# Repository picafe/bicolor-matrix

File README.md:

# bicolor-matrix

> **This repository has moved to [bicolor-matrix-v2](https://github.com/picafe/bicolor-matrix-v2).**

A 32x8 bicolor LED matrix module composed of 4 8x8 matrices based on the Holtek HT16K33A I2C LED driver.

## Inspiration

Inspired by the common 32x8 red LED matrix modules that use the MAX7219 IC, I wanted to make my own module but with more colours and functionality, while keeping the same asthetic. 

I found [these](https://www.aliexpress.com/item/1005007029570407.html) modules while browsing Aliexpress and thought they could look be a cool alternative. With the red and light green variant, you can have red, a light green, and orange all in one module. As far as I'm aware, there aren't RGB modules in a similar form factor, although you can take generic WS2818 8x8 matricies and 3D print a diffuser for them, although the footprint is much bigger. This project was also partially inspired by [bitluni's LED magnet tiles](https://www.youtube.com/watch?v=L2J_eNgjxio) which I found really cool.

Unlike the single colour matricies with 16 pins, these had 24. I found [this](https://www.adafruit.com/product/902) Adafruit module and followed a similar schematic with the Holtek HT16K33A I2C LED driver, but with an inverted board layout, and with 4 modules on one PCB. This was my 2nd PCB project, so it was definately a big undertaking.

## Showcase

Matrix Board:

Adapter Board:
This adds functionality through a RP2040 Zero board, a DS3231 module and a small buzzer, and a generic logic level shifter since the Holtek IC only operates near 5V.

Button Board:
An addition to the adapter board and provides 4 interface buttons for setting time

## Bill of Materials (BOM) + Assembly Notes
Item | Quantity | Description
| -------- | ------- | ------- |
[Machine Pin Headers](https://www.aliexpress.com/item/10000000838267.html) | 5 Pcs | 2.54mm pitch circular pin headers to connect the LED matricies to the main PCB. These are needed such as to not solder the matrix boards directly to the PCB, allowing for easier replacement if needed.
12mm x 12mm Buttons | 4 | Generic 12mm tactile push buttons, whatever is cheapest on Aliexpress. I used [these](https://www.aliexpress.com/item/10000000838267.html).
RP2040 Zero | 1 | Microcontroller board, whatever is cheapest on Aliexpress. I bought from [here](https://www.aliexpress.com/item/1005007650325892.html).
[DS3231 Module](https://www.aliexpress.com/item/1005007143842437.html) | 1 | Mini module without the battery, basically a simple breakout. Use side cutters to cut the plastic on the pre-soldered female headers, then desolder each of the pins. Solder in male headers.
Level Shifter | 1 | 4-channel logic level shifter module, whatever is cheapest on Aliexpress. They are cheapest in packs of 10, so you can use the extra ones for other projects. I bought from [here](https://www.aliexpress.com/item/1005006765742290.html).
Buzzer | 1 | Generic 3.3V 7.6mm diameter buzzer, whatever is cheapest on Aliexpress.
[Right Angle Pin Headers](https://www.aliexpress.com/item/32896209964.html) | 1 | Get the R1 type of pin headers pictured here, they're slightly more uncommon and more expensive than the R1 type. This is for the button board connection. 
2.54mm Pin Headers (Male and Female) | 1 | To connect the matrix board to the adapter board and general use. This [video](https://www.youtube.com/watch?v=qDG3VFSMSPQ) shows how to make custom length female headers.

Buying Note: I recommend you try to buy components on the Aliexpress mobile app (web on desktop doesn't seem to have a search bar) in Bundle Deals if you can find them as you can get better prices, and they usually ship faster.

Ordering Note: I recommend you to create your own adapter board for the project. The one I built has some design flaws (button board doesn't fit flush with the adapter board, the right angle headers need to be positioned lower, and usb connector placement could be improved).

It was designed to be a prototype and optimize costs, so I recommend you to make your own design based on your needs. I was browsing Aliexpress a few days ago and found this [RP2350 stamp module](https://www.aliexpress.com/item/1005008513193739.html) which would make a better alternative since you can position the USB connector anywhere on the PCB. It's also relatively cheap.

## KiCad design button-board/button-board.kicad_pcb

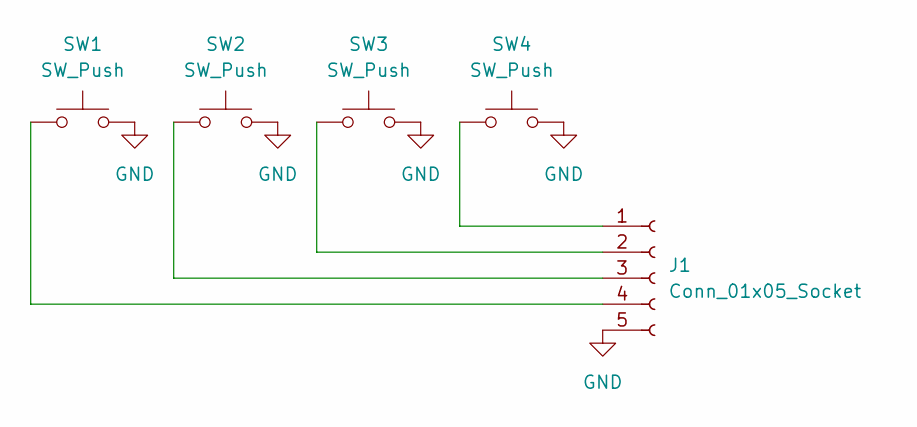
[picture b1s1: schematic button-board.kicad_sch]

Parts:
J1: Conn_01x05_Socket; PinSocket_1x05_P2.54mm_Vertical
SW1, SW2, SW3, SW4: SW_Push; SW_PUSH-12mm

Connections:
GND: J1.5, SW1.2, SW2.2, SW3.2, SW4.2
unnamed: J1.1, SW4.1
unnamed: J1.2, SW3.1
unnamed: J1.3, SW2.1
unnamed: J1.4, SW1.1

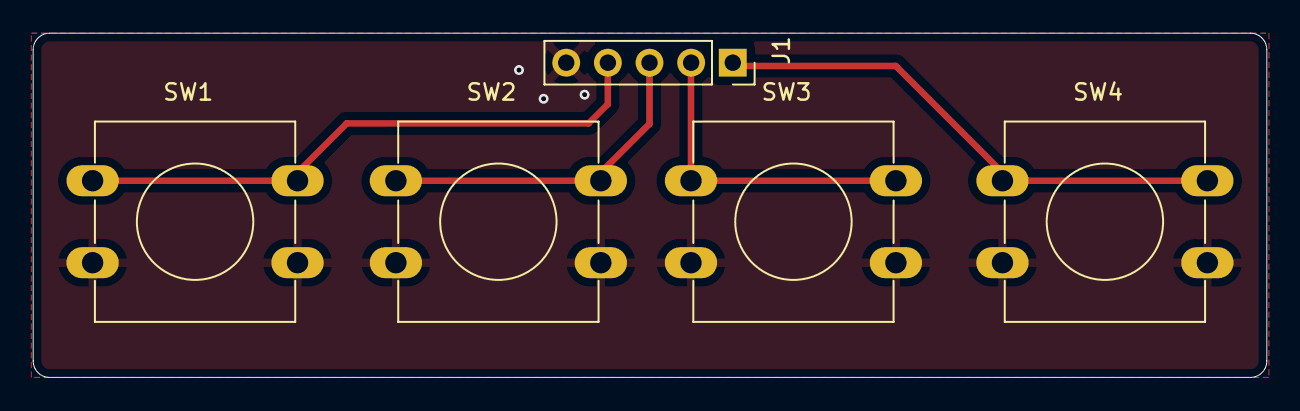
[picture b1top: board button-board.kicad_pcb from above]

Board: 2 copper layers, 75.3 x 21.0 mm, 5 parts (0 on the bottom side), 5 nets.

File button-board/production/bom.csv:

Designator,Footprint,Quantity,Value,LCSC Part #
J1,PinSocket_1x05_P2.54mm_Vertical,1,Conn_01x05_Socket,
"SW1, SW2, SW3, SW4",SW_PUSH-12mm,4,SW_Push,

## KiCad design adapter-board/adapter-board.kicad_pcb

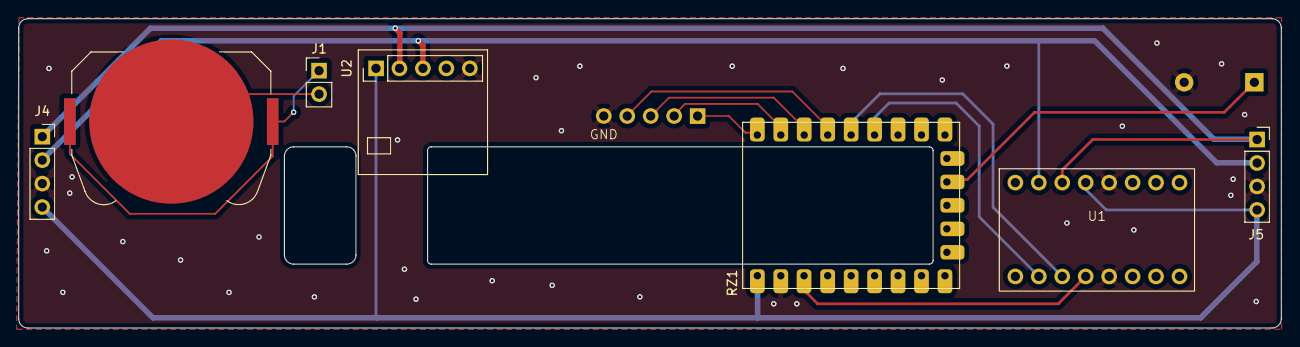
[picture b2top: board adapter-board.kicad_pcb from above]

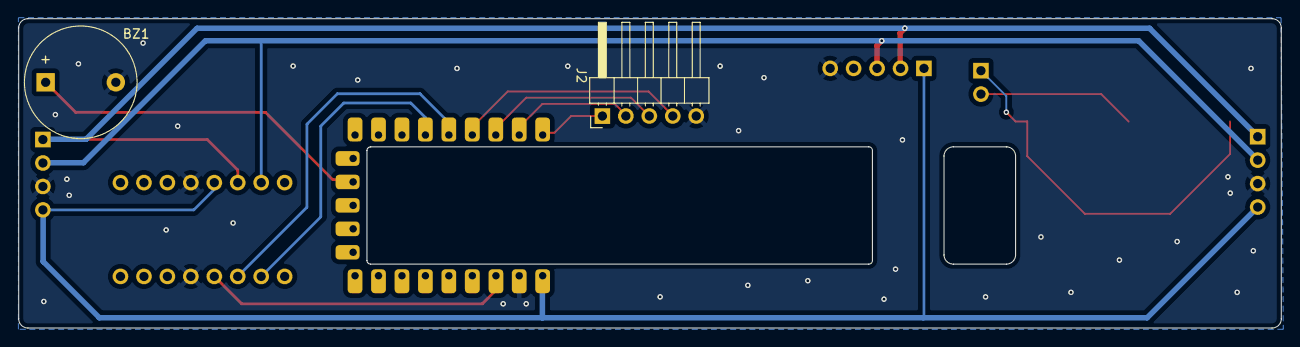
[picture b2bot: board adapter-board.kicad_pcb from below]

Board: 2 copper layers, 136.8 x 33.5 mm, 9 parts (2 on the bottom side), 12 nets.

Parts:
BT1: Battery_Cell; BatteryHolder_Keystone_3034_1x20mm
BZ1: Buzzer; Buzzer_12x9.5RM7.6
J1: Conn_01x02_Socket; PinHeader_1x02_P2.54mm_Vertical
J2: Conn_01x05_Pin; PinHeader_1x05_P2.54mm_Horizontal
J4, J5: Conn_01x04_Socket; PinSocket_1x04_P2.54mm_Vertical
RZ1: RP2040-Zero
U1: Generic-Level-Shifter
U2: PinHeader_1x05_P2.54mm_Vertical

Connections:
3V3: RZ1.21 (3V3), U1.9 (LV)
GND: BZ1.2 (-), J2.5, J4.3, J5.3, RZ1.22 (GND), U1.4 (GND), U1.10 (GND), U2.5 (GND)
unnamed: BZ1.1 (+), RZ1.11 (GP10)
unnamed: J2.1, RZ1.1 (GP0)
unnamed: J2.2, RZ1.2 (GP1)
unnamed: J2.3, RZ1.3 (GP2)
unnamed: J2.4, RZ1.4 (GP3)
unnamed: J4.1, J5.1, U1.2 (HV2), U2.2 (SDA)
unnamed: J4.2, J5.2, U1.1 (HV1), U2.3 (SCL)
unnamed: RZ1.5 (GP4), U1.8 (LV2)
unnamed: RZ1.6 (GP5), U1.7 (LV1)
VUSB: J4.4, J5.4, RZ1.23 (5V), U1.3 (HV), U2.1 (VCC)

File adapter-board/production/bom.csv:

Designator,Footprint,Quantity,Value,LCSC Part #
BT1,BatteryHolder_Keystone_3034_1x20mm,1,Battery_Cell,
BZ1,Buzzer_12x9.5RM7.6,1,Buzzer,
J1,PinHeader_1x02_P2.54mm_Vertical,1,Conn_01x02_Socket,
J2,PinHeader_1x05_P2.54mm_Horizontal,1,Conn_01x05_Pin,
"J4, J5",PinSocket_1x04_P2.54mm_Vertical,2,Conn_01x04_Socket,
RZ1,RP2040-Zero,1,RP2040-Zero,
U1,Generic-Level-Shifter,1,~,
U2,PinHeader_1x05_P2.54mm_Vertical,1,~,

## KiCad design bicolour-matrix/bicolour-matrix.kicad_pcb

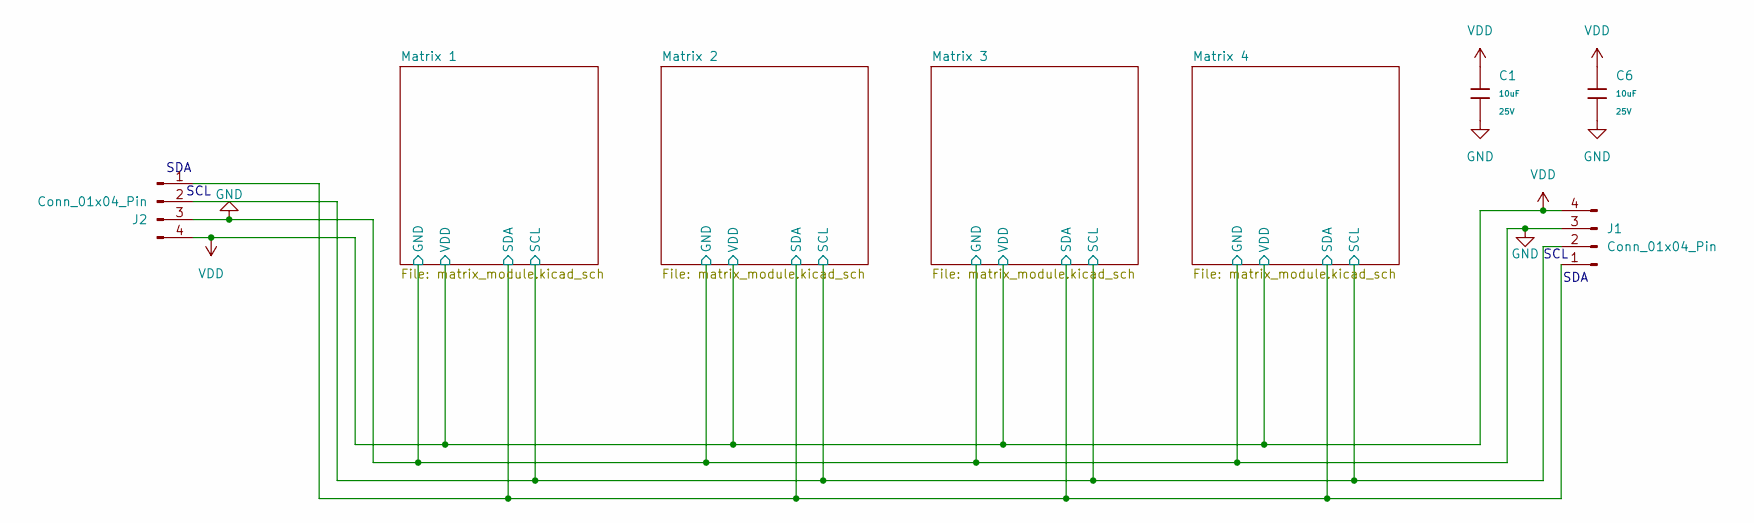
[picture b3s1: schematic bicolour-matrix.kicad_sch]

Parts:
C1, C6: 10uF; C_0805; Voltage Rated 25V; Tolerance ±10%; Part CL21A106KAYNNNE; LCSC C15850
J1, J2: Conn_01x04_Pin; PinHeader_1x04_P2.54mm_Vertical

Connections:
/Matrix 1/SCL: J1.2, J2.2; also elsewhere on the board
/Matrix 1/SDA: J1.1, J2.1; also elsewhere on the board
GND: C1.2, C6.2, J1.3, J2.3; also elsewhere on the board
VDD: C1.1, C6.1, J1.4, J2.4; also elsewhere on the board

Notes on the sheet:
SCL
SDA

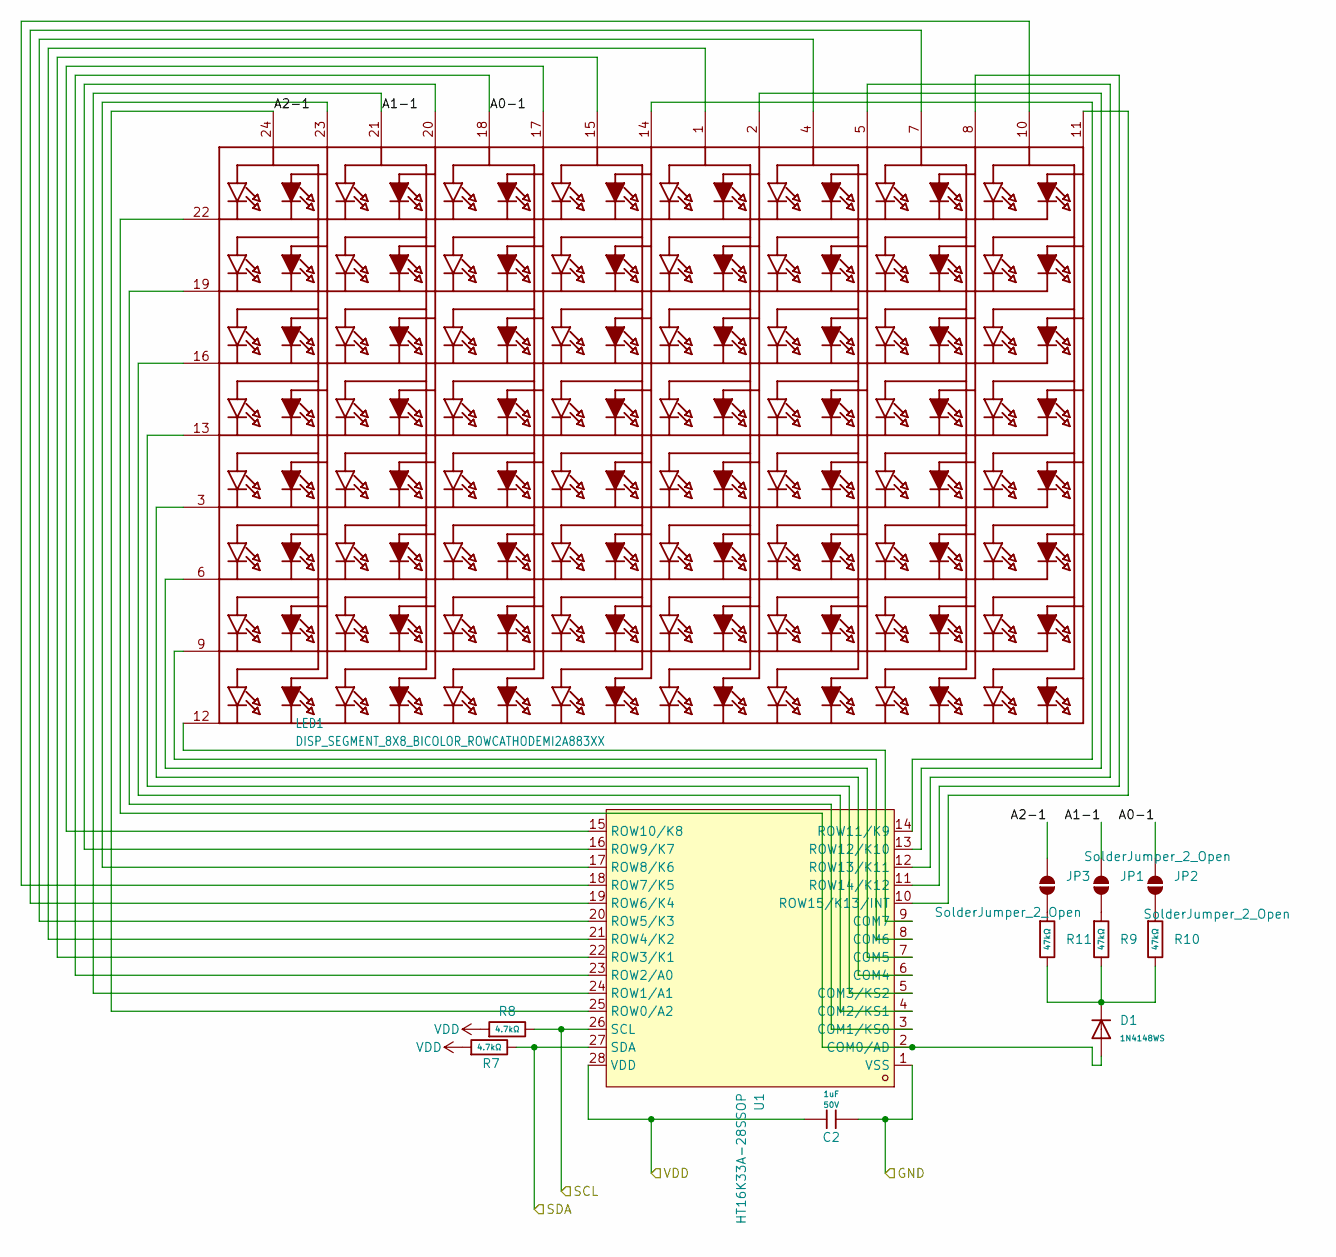
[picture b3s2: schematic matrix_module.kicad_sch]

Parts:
C2: 1uF; C_0603; Voltage Rated 50V; Tolerance ±10%; Part CL10A105KB8NNNC; LCSC C15849
D1: 1N4148WS; D_SOD-323; Forward Voltage (Vf@If) 1.25V@150mA; Reverse Voltage (Vr) 100V; Part 1N4148WS; LCSC C2128
JP1, JP2, JP3: SolderJumper_2_Open; SolderJumper-2_P1.3mm_Open_RoundedPad1.0x1.5mm
LED1: DISP_SEGMENT_8X8_BICOLOR_ROWCATHODEMI2A883XX; SEGMENT_BICOL_BL-M12A883XX
R7, R8: 4.7kΩ; R_0603; Overload Voltage (Max) 75V; Tolerance ±1%; Part 0603WAF4701T5E; LCSC C23162
R9, R10, R11: 47kΩ; R_0603; Overload Voltage (Max) 75V; Tolerance ±1%; Part 0603WAF4702T5E; LCSC C25819
U1: HT16K33A-28SSOP; SSOP-28_3.9x9.9mm_P0.635mm; LCSC Part C5444738

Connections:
/Matrix 1/A0-1: JP2.2 (B), LED1.18 (A5), U1.23 (ROW2/A0)
/Matrix 1/A1-1: JP1.2 (B), LED1.21 (A3), U1.24 (ROW1/A1)
/Matrix 1/A2-1: JP3.2 (B), LED1.24 (A1), U1.25 (ROW0/A2)
/Matrix 1/SCL: R8.2, U1.26 (SCL); also elsewhere on the board
/Matrix 1/SDA: R7.2, U1.27 (SDA); also elsewhere on the board
GND: C2.2, U1.1 (VSS); also elsewhere on the board
unnamed: D1.1, R9.2, R10.2, R11.2
unnamed: JP1.1 (A), R9.1
unnamed: JP2.1 (A), R10.1
unnamed: JP3.1 (A), R11.1
unnamed: LED1.23 (A2), U1.17 (ROW8/K6)
unnamed: LED1.20 (A4), U1.16 (ROW9/K7)
unnamed: LED1.17 (A6), U1.15 (ROW10/K8)
unnamed: LED1.15 (A7), U1.22 (ROW3/K1)
unnamed: LED1.14 (A8), U1.14 (ROW11/K9)
unnamed: LED1.1 (A9), U1.21 (ROW4/K2)
unnamed: LED1.2 (A10), U1.13 (ROW12/K10)
unnamed: LED1.4 (A11), U1.20 (ROW5/K3)
unnamed: LED1.5 (A12), U1.12 (ROW13/K11)
unnamed: LED1.7 (A13), U1.19 (ROW6/K4)
unnamed: LED1.8 (A14), U1.11 (ROW14/K12)
unnamed: LED1.10 (A15), U1.18 (ROW7/K5)
unnamed: LED1.11 (A16), U1.10 (ROW15/K13/INT)
unnamed: D1.2, LED1.22 (K1), U1.2 (COM0/AD)
unnamed: LED1.19 (K2), U1.3 (COM1/KS0)
unnamed: LED1.16 (K3), U1.4 (COM2/KS1)
unnamed: LED1.13 (K4), U1.5 (COM3/KS2)
unnamed: LED1.3 (K5), U1.6 (COM4)
unnamed: LED1.6 (K6), U1.7 (COM5)
unnamed: LED1.9 (K7), U1.8 (COM6)
unnamed: LED1.12 (K8), U1.9 (COM7)
VDD: C2.1, R7.1, R8.1, U1.28 (VDD); also elsewhere on the board

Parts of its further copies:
C3, C4, C5: 1uF; C_0603; Voltage Rated 50V; Tolerance ±10%; Part CL10A105KB8NNNC; LCSC C15849
D2, D3, D4: 1N4148WS; D_SOD-323; Forward Voltage (Vf@If) 1.25V@150mA; Reverse Voltage (Vr) 100V; Part 1N4148WS; LCSC C2128
JP4, JP5, JP6, JP7, JP8, JP9, JP10, JP11, JP12: SolderJumper_2_Open; SolderJumper-2_P1.3mm_Open_RoundedPad1.0x1.5mm
LED2, LED3, LED4: DISP_SEGMENT_8X8_BICOLOR_ROWCATHODEMI2A883XX; SEGMENT_BICOL_BL-M12A883XX
R1, R2, R6, R12, R16, R17: 4.7kΩ; R_0603; Overload Voltage (Max) 75V; Tolerance ±1%; Part 0603WAF4701T5E; LCSC C23162
R3, R4, R5, R13, R14, R15, R18, R19, R20: 47kΩ; R_0603; Overload Voltage (Max) 75V; Tolerance ±1%; Part 0603WAF4702T5E; LCSC C25819
U2, U3, U4: HT16K33A-28SSOP; SSOP-28_3.9x9.9mm_P0.635mm; LCSC Part C5444738

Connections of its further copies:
/Matrix 1/SCL: R2.2, R12.2, R17.2, U2.26 (SCL), U3.26 (SCL), U4.26 (SCL); also elsewhere on the board
/Matrix 1/SDA: R1.2, R6.2, R16.2, U2.27 (SDA), U3.27 (SDA), U4.27 (SDA); also elsewhere on the board
/Matrix 2/A0-1: JP6.2 (B), LED2.18 (A5), U2.23 (ROW2/A0)
/Matrix 2/A1-1: JP5.2 (B), LED2.21 (A3), U2.24 (ROW1/A1)
/Matrix 2/A2-1: JP4.2 (B), LED2.24 (A1), U2.25 (ROW0/A2)
/Matrix 3/A0-1: JP9.2 (B), LED3.18 (A5), U3.23 (ROW2/A0)
/Matrix 3/A1-1: JP8.2 (B), LED3.21 (A3), U3.24 (ROW1/A1)
/Matrix 3/A2-1: JP7.2 (B), LED3.24 (A1), U3.25 (ROW0/A2)
/Matrix 4/A0-1: JP12.2 (B), LED4.18 (A5), U4.23 (ROW2/A0)
/Matrix 4/A1-1: JP11.2 (B), LED4.21 (A3), U4.24 (ROW1/A1)
/Matrix 4/A2-1: JP10.2 (B), LED4.24 (A1), U4.25 (ROW0/A2)
GND: C3.2, C4.2, C5.2, U2.1 (VSS), U3.1 (VSS), U4.1 (VSS); also elsewhere on the board
unnamed: D2.1, R3.2, R4.2, R5.2
unnamed: D3.1, R13.2, R14.2, R15.2
unnamed: D4.1, R18.2, R19.2, R20.2
unnamed: JP4.1 (A), R3.1
unnamed: JP5.1 (A), R4.1
unnamed: JP6.1 (A), R5.1
unnamed: JP7.1 (A), R13.1
unnamed: JP8.1 (A), R14.1
unnamed: JP9.1 (A), R15.1
unnamed: JP10.1 (A), R18.1
unnamed: JP11.1 (A), R19.1
unnamed: JP12.1 (A), R20.1
unnamed: LED2.23 (A2), U2.17 (ROW8/K6)
unnamed: LED2.20 (A4), U2.16 (ROW9/K7)
unnamed: LED2.17 (A6), U2.15 (ROW10/K8)
unnamed: LED2.15 (A7), U2.22 (ROW3/K1)
unnamed: LED2.14 (A8), U2.14 (ROW11/K9)
unnamed: LED2.1 (A9), U2.21 (ROW4/K2)
unnamed: LED2.2 (A10), U2.13 (ROW12/K10)
unnamed: LED2.4 (A11), U2.20 (ROW5/K3)
unnamed: LED2.5 (A12), U2.12 (ROW13/K11)
unnamed: LED2.7 (A13), U2.19 (ROW6/K4)
unnamed: LED2.8 (A14), U2.11 (ROW14/K12)
unnamed: LED2.10 (A15), U2.18 (ROW7/K5)
unnamed: LED2.11 (A16), U2.10 (ROW15/K13/INT)
unnamed: D2.2, LED2.22 (K1), U2.2 (COM0/AD)
unnamed: LED2.19 (K2), U2.3 (COM1/KS0)
unnamed: LED2.16 (K3), U2.4 (COM2/KS1)
unnamed: LED2.13 (K4), U2.5 (COM3/KS2)
unnamed: LED2.3 (K5), U2.6 (COM4)
unnamed: LED2.6 (K6), U2.7 (COM5)
unnamed: LED2.9 (K7), U2.8 (COM6)
unnamed: LED2.12 (K8), U2.9 (COM7)
unnamed: LED3.23 (A2), U3.17 (ROW8/K6)
unnamed: LED3.20 (A4), U3.16 (ROW9/K7)
unnamed: LED3.17 (A6), U3.15 (ROW10/K8)
unnamed: LED3.15 (A7), U3.22 (ROW3/K1)
unnamed: LED3.14 (A8), U3.14 (ROW11/K9)
unnamed: LED3.1 (A9), U3.21 (ROW4/K2)
unnamed: LED3.2 (A10), U3.13 (ROW12/K10)
unnamed: LED3.4 (A11), U3.20 (ROW5/K3)
unnamed: LED3.5 (A12), U3.12 (ROW13/K11)
unnamed: LED3.7 (A13), U3.19 (ROW6/K4)
unnamed: LED3.8 (A14), U3.11 (ROW14/K12)
unnamed: LED3.10 (A15), U3.18 (ROW7/K5)
unnamed: LED3.11 (A16), U3.10 (ROW15/K13/INT)
unnamed: D3.2, LED3.22 (K1), U3.2 (COM0/AD)
unnamed: LED3.19 (K2), U3.3 (COM1/KS0)
unnamed: LED3.16 (K3), U3.4 (COM2/KS1)
unnamed: LED3.13 (K4), U3.5 (COM3/KS2)
unnamed: LED3.3 (K5), U3.6 (COM4)
unnamed: LED3.6 (K6), U3.7 (COM5)
unnamed: LED3.9 (K7), U3.8 (COM6)
unnamed: LED3.12 (K8), U3.9 (COM7)
unnamed: LED4.23 (A2), U4.17 (ROW8/K6)
unnamed: LED4.20 (A4), U4.16 (ROW9/K7)
unnamed: LED4.17 (A6), U4.15 (ROW10/K8)
unnamed: LED4.15 (A7), U4.22 (ROW3/K1)
unnamed: LED4.14 (A8), U4.14 (ROW11/K9)
unnamed: LED4.1 (A9), U4.21 (ROW4/K2)
unnamed: LED4.2 (A10), U4.13 (ROW12/K10)
unnamed: LED4.4 (A11), U4.20 (ROW5/K3)
unnamed: LED4.5 (A12), U4.12 (ROW13/K11)
unnamed: LED4.7 (A13), U4.19 (ROW6/K4)
unnamed: LED4.8 (A14), U4.11 (ROW14/K12)
unnamed: LED4.10 (A15), U4.18 (ROW7/K5)
unnamed: LED4.11 (A16), U4.10 (ROW15/K13/INT)
unnamed: D4.2, LED4.22 (K1), U4.2 (COM0/AD)
unnamed: LED4.19 (K2), U4.3 (COM1/KS0)
unnamed: LED4.16 (K3), U4.4 (COM2/KS1)
unnamed: LED4.13 (K4), U4.5 (COM3/KS2)
unnamed: LED4.3 (K5), U4.6 (COM4)
unnamed: LED4.6 (K6), U4.7 (COM5)
unnamed: LED4.9 (K7), U4.8 (COM6)
unnamed: LED4.12 (K8), U4.9 (COM7)
VDD: C3.1, C4.1, C5.1, R1.1, R2.1, R6.1, R12.1, R16.1, R17.1, U2.28 (VDD), U3.28 (VDD), U4.28 (VDD); also elsewhere on the board

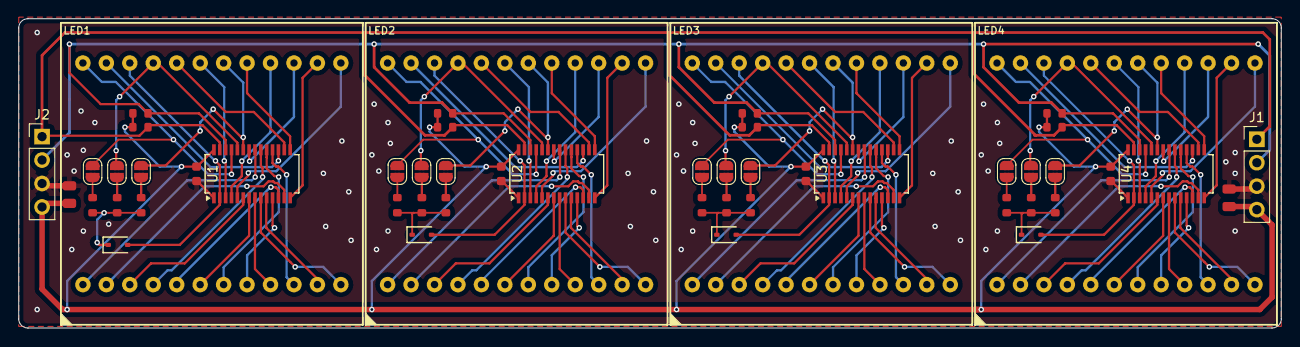
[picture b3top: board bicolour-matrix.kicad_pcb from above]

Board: 2 copper layers, 136.8 x 33.5 mm, 52 parts (0 on the bottom side), 116 nets.

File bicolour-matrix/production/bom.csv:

Designator,Footprint,Quantity,Value,LCSC Part #
"C1, C6",C_0805,2,10uF,C15850
"C2, C3, C4, C5",C_0603,4,1uF,C15849
"D1, D2, D3, D4",D_SOD-323,4,1N4148WS,C2128
"J1, J2",PinHeader_1x04_P2.54mm_Vertical,2,Conn_01x04_Pin,
"LED1, LED2, LED3, LED4",SEGMENT_BICOL_BL-M12A883XX,4,DISP_SEGMENT_8X8_BICOLOR_ROWCATHODEMI2A883XX,
"R1, R12, R16, R17, R2, R6, R7, R8",R_0603,8,4.7kΩ,C23162
"R10, R11, R13, R14, R15, R18, R19, R20, R3, R4, R5, R9",R_0603,12,47kΩ,C25819
"U1, U2, U3, U4",SSOP-28_3.9x9.9mm_P0.635mm,4,HT16K33A-28SSOP,C5444738

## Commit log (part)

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2025-05-20 progress !!
2025-05-20 small idea
2025-05-27 feat: journal update
2025-07-16 feat: journal updates i forgot to commit
2025-08-11 feat: PCB
2025-08-14 feat: final revs
2025-08-14 feat: gerbers + design feedback
2025-08-16 feat: adapter board
2025-08-21 feat: adapter board kicad
2025-08-22 feat: gerbers
2025-08-22 feat: final changes
2025-08-26 feat: docs + gerbers
2025-08-26 feat: updated gerbers
2025-08-27 feat: fixed lcsc component
2025-11-20 Add project update notice to README
2025-12-30 feat: update readme
2025-12-30 feat: PCB updates
